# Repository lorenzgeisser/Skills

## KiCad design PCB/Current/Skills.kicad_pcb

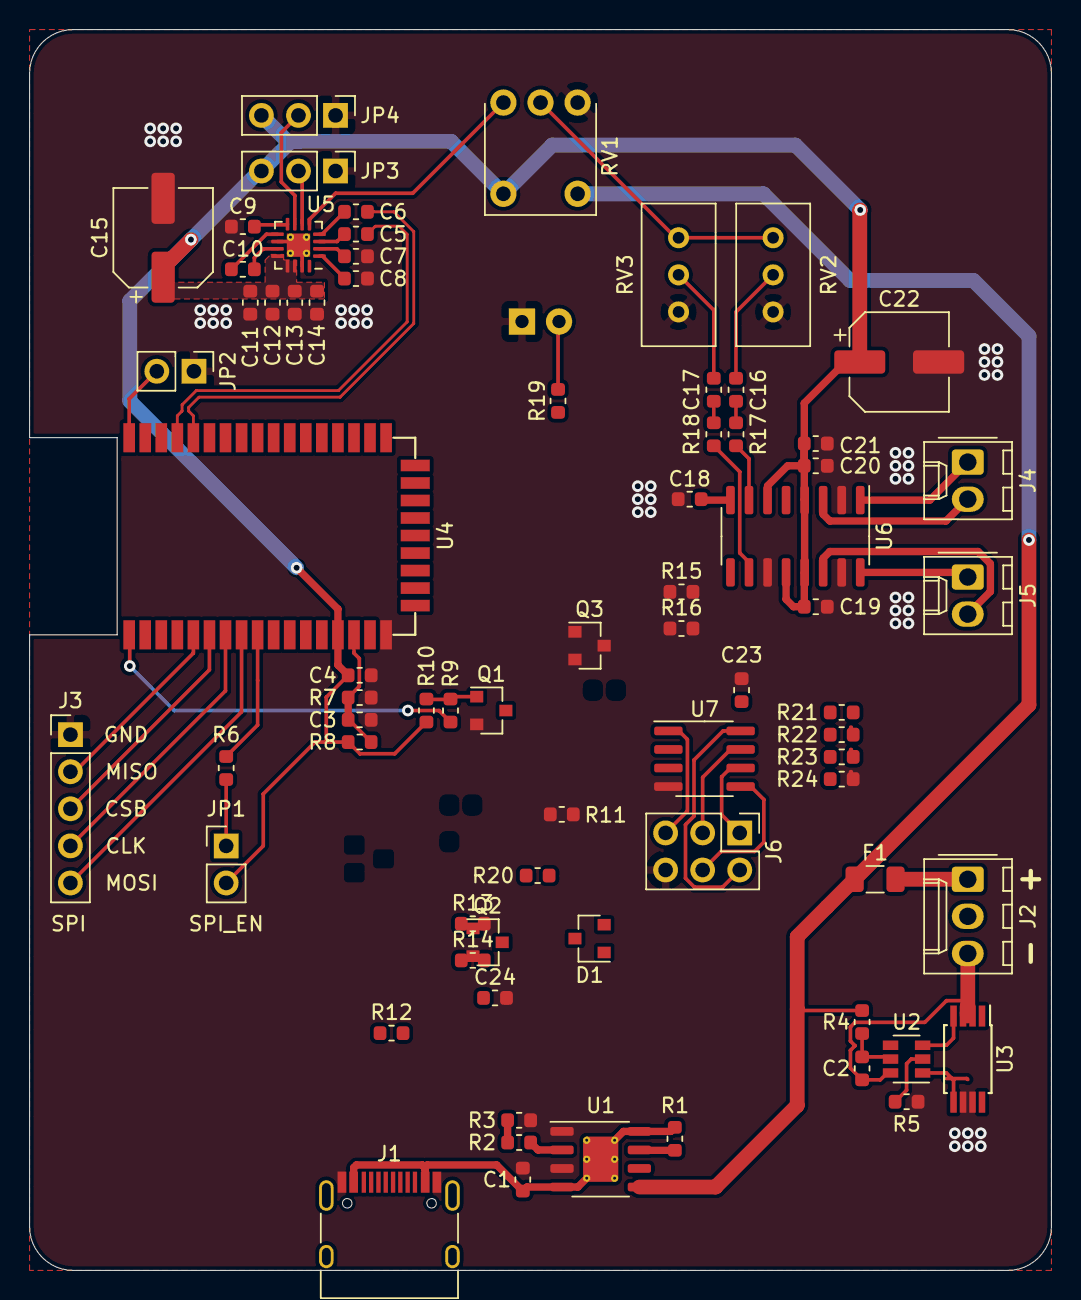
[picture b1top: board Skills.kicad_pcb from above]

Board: 2 copper layers, 70.0 x 85.0 mm, 74 parts (1 on the bottom side), 60 nets.

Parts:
C1, C2, C4, C9, C10, C11, C12, C13, C14, C18, C19, C20, C21, C23, C24: 1uF; C_0603_1608Metric
C3: 10u; C_0603_1608Metric
C5, C6, C7, C8, C16, C17: 470nF; C_0603_1608Metric
C15, C22: 100uF; CP_Elec_6.3x7.7
D1: BAT54C; SOT-23
D2: LED; LED_D5.0mm_Horizontal_O1.27mm_Z3.0mm_Clear
F1: 5A; Fuse_1206_3216Metric
J1: USB_C_Receptacle_USB2.0; USB_C_Receptacle_HRO_TYPE-C-31-M-12
J2: BATT; Molex_KK-254_AE-6410-03A_1x03_P2.54mm_Vertical
J3: SPI; PinHeader_1x05_P2.54mm_Vertical
J4: L; Molex_KK-254_AE-6410-02A_1x02_P2.54mm_Vertical
J5: R; Molex_KK-254_AE-6410-02A_1x02_P2.54mm_Vertical
J6: Conn_01x06; PinHeader_2x03_P2.54mm_Vertical
JP1: SPI_EN; PinHeader_1x02_P2.54mm_Vertical
JP2: AGND; PinHeader_1x02_P2.54mm_Vertical
JP3, JP4: Jumper_NC_Dual; PinHeader_1x03_P2.54mm_Vertical
Q1, Q2: AO3400; SOT-23
Q3: AO3401; SOT-23
R1, R6, R7, R8, R10, R11, R13, R14, R16, R17, R18, R20: 10k; R_0603_1608Metric
R2, R3, R5, R9, R12, R15, R19, R21, R22, R23, R24: 1k; R_0603_1608Metric
R4: 100; R_0603_1608Metric
RV1: pot_sw; POT_SW
RV2, RV3: R_POT; Potentiometer_Bourns_3296W_Vertical
U1: TP4056; HSOP-8-1EP_3.9x4.9mm_P1.27mm_EP2.41x3.1mm_ThermalVias
U2: FS312F; SOT-23-6
U3: FS8205A; TSSOP-8_4.4x3mm_P0.65mm
U4: F-3188
U5: TPA6132A2RTE; WQFN-16-1EP_3x3mm_P0.5mm_EP1.6x1.6mm_ThermalVias
U6: PAM8403; SOIC-16_3.9x9.9mm_P1.27mm
U7: ATtiny13A; SOIC-8_3.9x4.9mm_P1.27mm

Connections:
+BATT: C4.1, C11.1, C12.1, C13.1, C14.1, C15.1, C19.1, C20.1, C21.1, C22.1, D1.2, JP1.2, JP3.3, JP4.3, Q3.3, R8.1, R10.1, R14.1, R20.1, R21.1, RV1.5, U4.14, U5.12, U5.13, U5.14, U6.4, U6.6, U6.12, U6.13
/+: C5.2, U4.40
/-: C6.2, U4.39
/mono: RV1.1, U5.5
Blue: Q1.3, R11.2, U7.2
CHRG: J6.1, R1.2, U1.7, U7.6
CLK: J3.4, U4.7
CSB: J3.3, U4.6
GND: C1.2, C3.2, C4.2, C7.2, C8.2, C9.2, C11.2, C12.2, C13.2, C14.2, C15.2, C18.2, C19.2, C20.2, C21.2, C22.2, C23.2, C24.2, D2.1, J1.A1, J1.A12, J1.B1, J1.B12, J3.1, J6.6, JP2.1, JP3.1, JP4.1, Q1.2, Q2.2, R3.2, R5.2, R7.2, R13.2, R16.2, R24.2, RV1.3, RV2.3, RV3.3, U1.1, U1.3, U3.6, U3.7, U4.17, U5.10, U5.15, U5.17, U6.2, U6.11, U6.15, U7.4
MISO: J3.2, U4.5
MOSI: J3.5, U4.8
MUTE: J6.4, R12.2, U7.5
unnamed: C2.1, R4.1, U2.5
unnamed: C2.2, J2.3, U2.6, U3.2, U3.3
unnamed: C3.1, R7.1, R8.2, U4.15
unnamed: C5.1, U5.3
unnamed: C6.1, U5.4
unnamed: C7.1, U5.2
unnamed: C8.1, U5.1
unnamed: C9.1, U5.8
unnamed: C10.1, U5.11
unnamed: C10.2, U5.9
unnamed: C16.1, R17.2
unnamed: C16.2, RV2.2
unnamed: C17.1, R18.1
unnamed: C17.2, RV3.2
unnamed: C18.1, U6.8
unnamed: C24.1, J6.3, R23.2, R24.1, U7.7
unnamed: D2.2, R19.2
unnamed: F1.1, R4.2, RV1.4, U1.5
unnamed: F1.2, J2.1
unnamed: J4.1, U6.1
unnamed: J4.2, U6.3
unnamed: J5.1, U6.16
unnamed: J5.2, U6.14
unnamed: J6.5, R20.2, U7.1
unnamed: JP1.1, R6.1
unnamed: JP2.2, U4.43
unnamed: JP3.2, U5.6
unnamed: JP4.2, U5.7
unnamed: Q1.1, R9.1, R10.2
unnamed: Q2.1, R12.1, R13.1
unnamed: Q2.3, R14.2, R15.2
unnamed: Q3.1, R15.1
unnamed: Q3.2, R16.1, U6.5
unnamed: R2.1, U1.2
unnamed: R2.2, R3.1
unnamed: R5.1, U2.2
unnamed: R9.2, U4.1
unnamed: R17.1, U6.7
unnamed: R18.2, U6.10
unnamed: R19.1, U7.3
unnamed: R21.2, R22.1
unnamed: R22.2, R23.1
unnamed: RV1.2, RV2.1, RV3.1
unnamed: U2.1, U3.5
unnamed: U2.3, U3.4
SPI_EN: R6.2, U4.9
VBUS: C1.1, D1.1, J1.A4, J1.A9, J1.B4, J1.B9, R1.1, U1.4, U1.8, U1.9
VCC: C23.1, D1.3, J6.2, R11.1, U7.8

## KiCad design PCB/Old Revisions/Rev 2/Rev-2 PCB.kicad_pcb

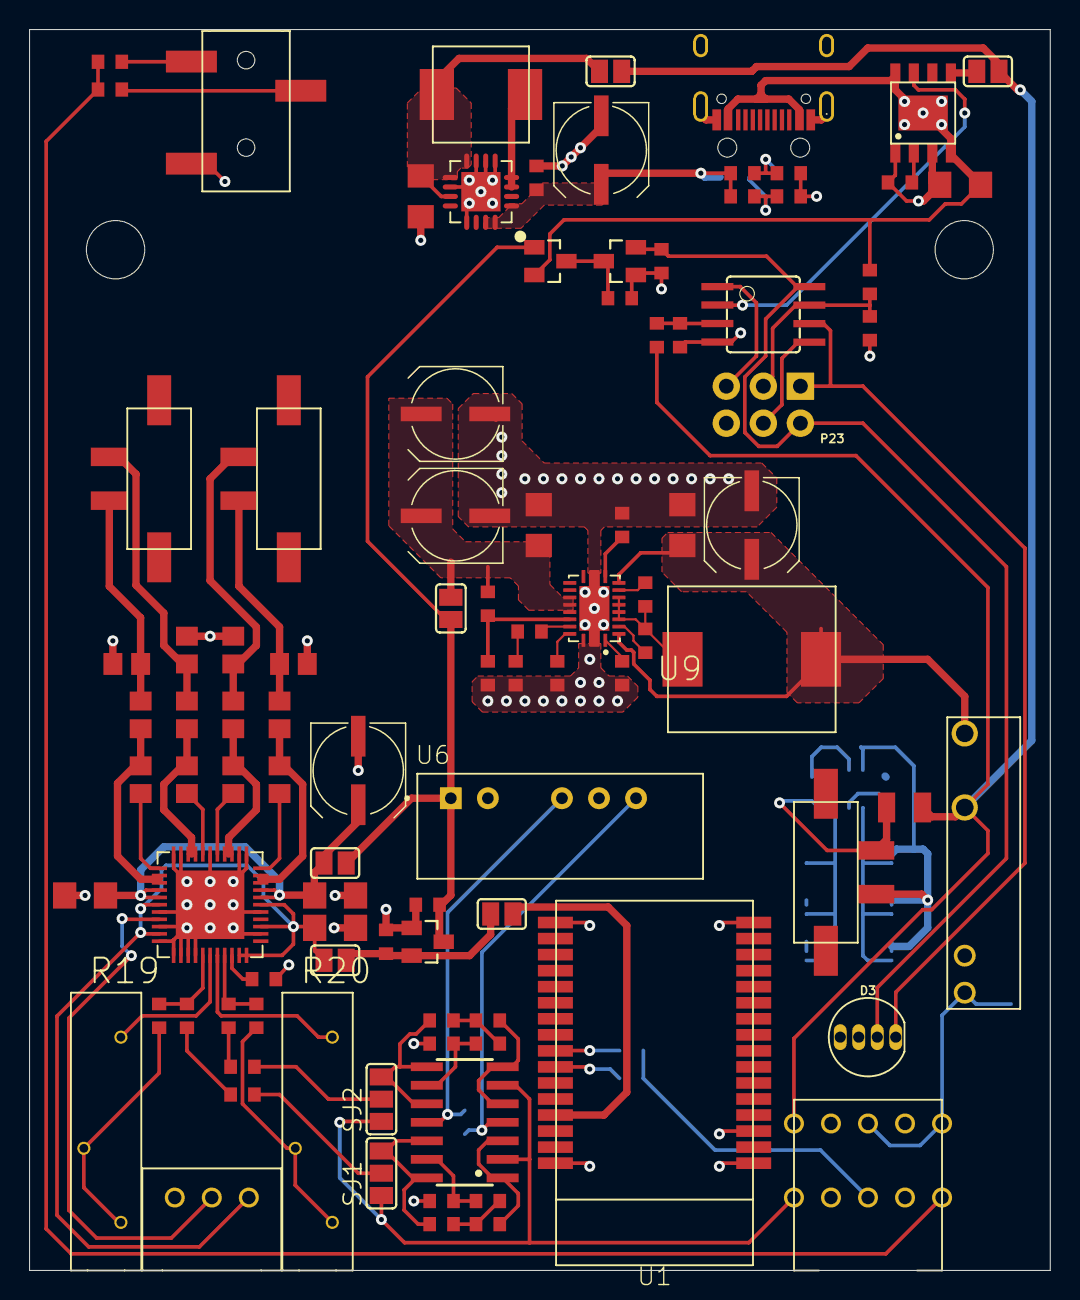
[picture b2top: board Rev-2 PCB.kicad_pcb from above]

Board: 2 copper layers, 70.0 x 85.1 mm, 112 parts (0 on the bottom side), 88 nets.

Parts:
@HOLE0, @HOLE1: (no value)
C1, C4, C13, C17: 10u; R0603
C2, C11, C12, C22, C24, C25, C27: 10u; 1206
C3, C9, C18: 100n; R0603
C5, C6, C7, C23: 1n; R0603
C8, C21: 10n; R0603
C10, C26, C28: 100u; UD-6,3X7,7_NICHICON
C14, C15: 470n; R0603
C16, C19, C29: 2.2u; R0603
C20, C30: 220u; UD-6,3X7,7_NICHICON
C31, C32, C33, C34: 100n; 0805
C35, C36, C37, C38: 470p; 0805
D1: DIODEDO-214AC; DO214AC
D2: BAS70-05; SOT23
D3: NEOPIXEL; LED-RGB-THRU
F1: 5A; FUSE_SMD
J1, J2, J3, J4, J5, J6: JUMPER_2S; SJ
K1: RELAY_2; RELAY
L1: 6.8u /4A; INDUCTOR234545
L2: 1.5u; INDUCTOR2345
L3, L4, L5, L6: INDUCTOR0805; 0805
P2: USB_TYPE-C; TYPE-C
P3: AUX; AUDIO
P4, P58, P59: HEADER_2MOLEX; MOLEX_43650_2P
P23: SPI-HEADERNS; 2X3-NS
P48: USB_TYPE-A; USB-A
Q1, Q2, Q3: FS8205; SOP65P640X120-8N
R1: 100; R0603
R2, R3, R4, R5: 1k; R0603
R6: 2k; R0603
R7: 1.1k; R0603
R8: 560; R0603
R9, R17, R18: 10k; R0603
R10, R12, R28: 100k; R0603
R11: 47k; R0603
R13: 180k; R0603
R14, R15: 30k; R0603
R16, R29: 255k; R0603
R19, R20: 20k; TRIMMPOTI
R21: 10k; POT
R22: 105k; R0603
R23: 43k; R0603
R24, R27: 49.9k; R0603
R25: 44.2k; R0603
R26: 75k; R0603
R30: 825k; R0603
R31: 92k; R0603
S1: SWITCH; FE06
SJ1, SJ2: SJ2W; SJ_2
U1: BK8000; WIRELESS-BLUETOOTH-BK8000
U2, U7: REG1118SOT23-3; SOT23
U3: FS312F; TSOT23-6
U4: TP4056; SOP-8
U5: QUAD_OP; SO14
U6: NMA; CONV_PCN2-S24-D15-S
U8: TPS6103X; PVQFN-16
U9: TPS61088; QFN50P450X350X100-21N
U10: TINY15LS; SOIC8
U11: MAX9744; TQFN44_7MM

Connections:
/3.3V_AMP: C22.1, J1.2, R21.1, U11.6, U11.10, U11.21, U11.22, U11.25, U11.28
/3.3V_BT: J2.2, U1.29
/5V: C19.1, C20.+, P48.VBUS, R23.2, R26.2, U8.1, U8.15, U8.16
/12V: C1.1, D2.1, J5.2, J6.2, U2.3, U6.1
/AUDIO: S1.P$6, SJ1.1, SJ2.1, U5.2, U5.6
/BATT_F: F1.2, J3.2, J4.1, K1.S1, R28.2, S1.P$5
/BATT_F_SW: C10.+, C11.1, K1.S2, L2.P$1, U9.2, U9.9
/BATT_SENSE: R28.1, R29.2, U10.3
/BATT_UNFUSED: F1.1, P4.1, R1.1
/MISO/NP: D3.1, P23.1, U10.6
/MOSI: P23.4, U10.5
/OP+: C6.1, U5.4, U6.6
/OP-: C6.2, U5.11, U6.4
/OUT_HP: C15.1, SJ2.2
/OUT_LP: C14.1, SJ1.2
/RST: P23.5, U10.1
/SCK/VBUS_DETECT: P23.3, R12.1, R13.2, U10.7
/TP_IND: U4.7, U10.2
/VBUS: C2.1, D2.2, P2.A4/B9, P2.B4/A9, R12.2, U4.4, U4.8, U4.PAD, U4.PAD2
GND: C1.2, C2.2, C4.2, C8.2, C10.-, C11.2, C12.2, C13.2, C16.2, C17.2, C19.2, C20.-, C21.2, C22.2, C23.2, C24.2, C25.2, C26.-, C27.2, C28.-, C29.2, C30.-, C35.2, C36.2, C37.1, C38.1, D1.A, D3.3, K1.C2, P2.A1/B12, P2.B1/A12, P2.P$1, P2.P$2, P2.P$3, P2.P$4, P2.P$5, P2.P$6, P2.P$7, P2.P$8, P2.P$9, P2.P$10, P2.P$11, P2.P$12, P2.P$13, P2.P$14, P2.P$15, P2.P$16, P2.P$17, P2.P$18, P2.P$19, P2.P$20, P2.P$21, P2.P$22, P2.P$23, P2.P$24, P2.P$25, P2.P$26, P2.P$27, P2.P$28, P2.P$29, P2.P$30, P2.P$31, P2.P$32, P2.P$33, P2.P$34, P2.P$35, P2.P$36, P2.P$37, P2.P$38, P3.P$3, P23.6, P48.GND, P48.S1, P48.S2, P48.S3, P48.S4, Q1.5, Q1.6, Q1.7, Q2.5, Q2.6, Q2.7, Q3.5, Q3.6, Q3.7, R6.1, R7.1, R10.1, R13.1, R21.3, R22.1, R24.1, R27.1, R29.1, R31.1, U1.1, U1.3, U1.16, U1.17, U1.32, U2.1, U3.3, U4.1, U4.3, U6.2, U6.5, U7.1, U8.5, U8.6, U8.7, U8.10, U8.13, U8.THERMAL, U8.THERMAL1, U9.20, U9.21, U9.22, U9.23, U10.4, U11.7, U11.9, U11.11, U11.12, U11.13, U11.14, U11.15, U11.24, U11.27, U11.34, U11.35, U11.39, U11.43, U11.44, U11.THERMAL, U11.THERMAL1
unnamed: C3.1, R1.2, U3.5
unnamed: C3.2, P4.2, Q1.2, Q1.3, Q2.2, Q2.3, Q3.2, Q3.3, U3.6
unnamed: C4.1, J1.1, J2.1, U2.2
unnamed: C5.1, U5.5, U5.7
unnamed: C5.2, C7.1, R11.1
unnamed: C7.2, R10.2, U5.9
unnamed: C8.1, R9.2, U5.13
unnamed: C9.1, R8.2, R9.1
unnamed: C9.2, SJ1.3, U5.12, U5.14
unnamed: C12.1, J4.2, L1.P$1, U8.8, U8.9, U8.11
unnamed: C13.1, D2.3, U7.3
unnamed: C14.2, R14.1
unnamed: C15.2, R15.1
unnamed: C16.1, U9.1
unnamed: C17.1, D3.2, P23.2, U7.2, U10.8
unnamed: C18.1, L2.P$2, R16.1, U9.4, U9.5, U9.6, U9.7
unnamed: C18.2, U9.8
unnamed: C21.1, U9.10
unnamed: C23.1, R25.2
unnamed: C24.1, C26.+, C28.+, J6.1, R30.2, U9.14, U9.15, U9.16
unnamed: C25.1, C27.1, C30.+, J5.1, U11.4, U11.5, U11.29, U11.30
unnamed: C29.1, U11.20
unnamed: C31.1, U11.1
unnamed: C31.2, L3.1, U11.2, U11.3
unnamed: C32.1, U11.40
unnamed: C32.2, L4.1, U11.41, U11.42
unnamed: C33.1, U11.33
unnamed: C33.2, L5.1, U11.31, U11.32
unnamed: C34.1, U11.38
unnamed: C34.2, L6.1, U11.36, U11.37
unnamed: C35.1, L3.2, P58.1
unnamed: C36.1, L5.2, P59.1
unnamed: C37.2, L4.2, P58.2
unnamed: C38.2, L6.2, P59.2
unnamed: D1.C, K1.C1, S1.P$1, S1.P$3
unnamed: J3.1, U4.5
unnamed: L1.P$2, U8.3, U8.4
unnamed: P2.A5, P2.B5
unnamed: P2.A6, P2.B6
unnamed: P2.A7, P2.B7
unnamed: P2.A8, P2.B8
unnamed: P3.P$1, R3.1
unnamed: P3.P$2, R2.1
unnamed: P48.D+, R26.1, R27.2
unnamed: P48.D-, R23.1, R24.2
unnamed: Q1.1, Q1.8
unnamed: Q1.4, Q2.4, Q3.4, U3.1
unnamed: Q2.1, Q2.8
unnamed: Q3.1, Q3.8
unnamed: R2.2, R3.2, S1.P$10
unnamed: R4.1, U1.26
unnamed: R4.2, R5.2, S1.P$8
unnamed: R5.1, U1.25
unnamed: R6.2, U3.2
unnamed: R7.2, U4.2
unnamed: R8.1, U5.1, U5.3
unnamed: R11.2, SJ2.3, U5.8, U5.10
unnamed: R14.2, R17.1, U11.16
unnamed: R15.2, R18.1, U11.19
unnamed: R16.2, U9.3
unnamed: R17.2, R19.2, R19.3
unnamed: R18.2, R20.2, R20.3
unnamed: R19.1, U11.17
unnamed: R20.1, U11.18
unnamed: R21.2, U11.8
unnamed: R22.2, U9.19
unnamed: R25.1, U9.18
unnamed: R30.1, R31.2, U9.17

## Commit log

2019-10-21 first
2019-10-21 in progress
2019-12-18 working
2019-12-23 restart
2019-12-23 new project
2020-01-09 changed plane
2020-01-10 add KicCad logo
2020-01-12 annotate
2020-01-13 gerber
2020-03-05 kain plan wa da söll
2020-06-02 work in progress
